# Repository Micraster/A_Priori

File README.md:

# A_Priori
A repository of Modules for A Priori synth. A 5V USB powered modular synth using a Eurorack form factor.

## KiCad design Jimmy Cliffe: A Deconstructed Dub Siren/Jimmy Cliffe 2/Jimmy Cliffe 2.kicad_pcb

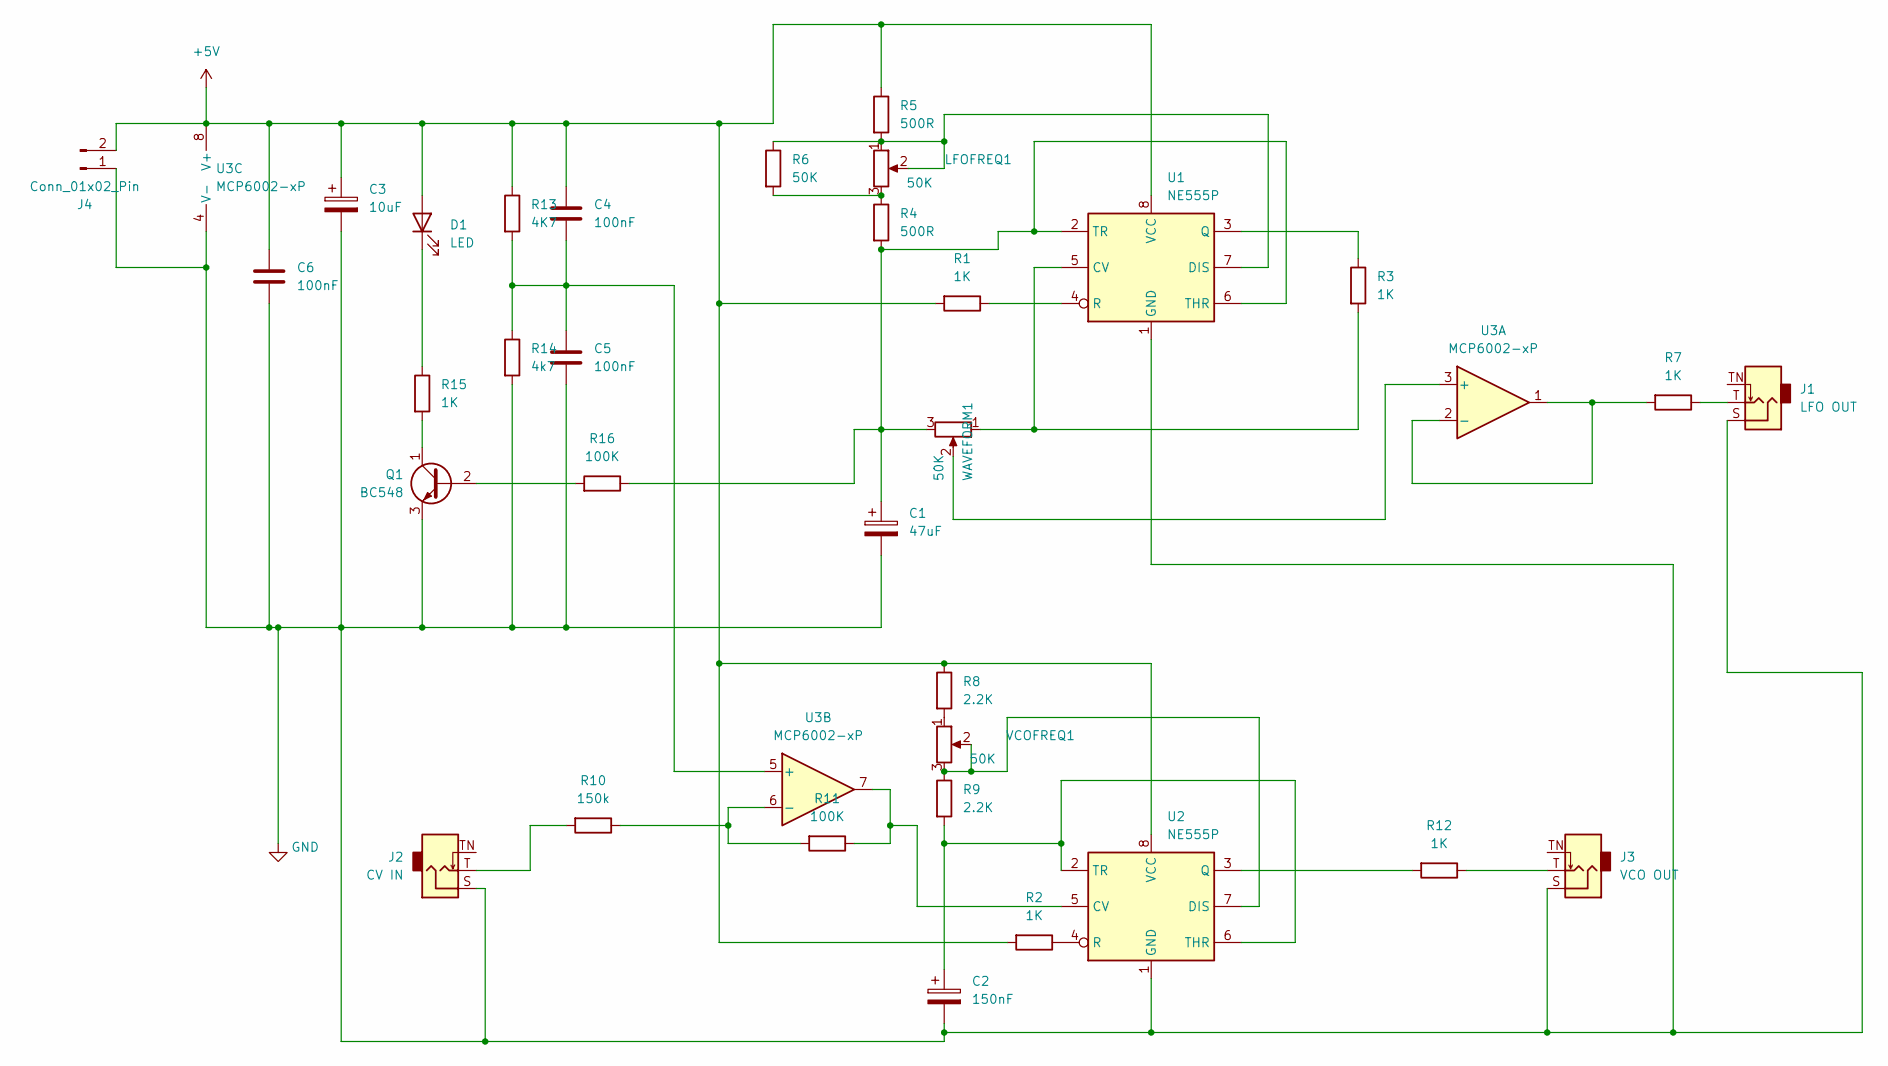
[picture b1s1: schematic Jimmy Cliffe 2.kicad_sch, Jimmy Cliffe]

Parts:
C1: 47uF; CP_Radial_D5.0mm_P2.50mm
C2: 150nF; C_Disc_D6.0mm_W2.5mm_P5.00mm
C3: 10uF; CP_Radial_D5.0mm_P2.50mm
C4, C5, C6: 100nF; C_Disc_D3.8mm_W2.6mm_P2.50mm
D1: LED; LED_D5.0mm
J1: LFO OUT; Jack_3.5mm_QingPu_WQP-PJ398SM_Vertical_CircularHoles
J2: CV IN; Jack_3.5mm_QingPu_WQP-PJ398SM_Vertical_CircularHoles
J3: VCO OUT; Jack_3.5mm_QingPu_WQP-PJ398SM_Vertical_CircularHoles
J4: Conn_01x02_Pin; JST_XH_B2B-XH-A_1x02_P2.50mm_Vertical
LFOFREQ1: 50K; TRIM_RV09AF-40-20K-A10K
Q1: BC548; TO-92_Inline
R1, R2, R3, R7, R12, R15: 1K; R_Axial_DIN0204_L3.6mm_D1.6mm_P7.62mm_Horizontal
R4, R5: 500R; R_Axial_DIN0204_L3.6mm_D1.6mm_P7.62mm_Horizontal
R6: 50K; R_Axial_DIN0204_L3.6mm_D1.6mm_P7.62mm_Horizontal
R8, R9: 2.2K; R_Axial_DIN0204_L3.6mm_D1.6mm_P7.62mm_Horizontal
R10: 150k; R_Axial_DIN0204_L3.6mm_D1.6mm_P7.62mm_Horizontal
R11: 100K; R_Axial_DIN0204_L3.6mm_D1.6mm_P7.62mm_Horizontal
R13: 4K7; R_Axial_DIN0204_L3.6mm_D1.6mm_P7.62mm_Horizontal
R14: 4k7; R_Axial_DIN0204_L3.6mm_D1.6mm_P7.62mm_Horizontal
R16: 100K; R_Axial_DIN0207_L6.3mm_D2.5mm_P7.62mm_Horizontal
U1, U2: NE555P; DIP-8_W7.62mm
U3: MCP6002-xP; DIP-8_W7.62mm
VCOFREQ1: 50K; TRIM_RV09AF-40-20K-A10K
WAVEFORM1: 50K; TRIM_RV09AF-40-20K-A10K

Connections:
+5V: C3.1, C4.1, C6.1, D1.2 (A), J4.2, R1.2, R2.2, R5.1, R8.1, R13.1, U1.8 (VCC), U2.8 (VCC), U3.8 (V+)
GND: C1.2, C2.2, C3.2, C5.2, C6.2, J1.S, J2.S, J3.S, J4.1, Q1.3 (E), R14.2, U1.1 (GND), U2.1 (GND), U3.4 (V-)
unnamed: D1.1 (K), R15.1
unnamed: J1.T, R7.1
unnamed: J2.T, R10.2
unnamed: J3.T, R12.1
unnamed: LFOFREQ1.3, R4.1, R6.2
unnamed: Q1.2 (B), R16.1
unnamed: Q1.1 (C), R15.2
unnamed: R8.2, VCOFREQ1.1
unnamed: R3.2, U1.5 (CV), WAVEFORM1.1
unnamed: LFOFREQ1.1, LFOFREQ1.2, R5.2, R6.1, U1.7 (DIS)
unnamed: R3.1, U1.3 (Q)
unnamed: R1.1, U1.4 (R)
unnamed: C1.1, R4.2, R16.2, U1.2 (TR), U1.6 (THR), WAVEFORM1.3
unnamed: R11.1, U2.5 (CV), U3.7
unnamed: R9.1, U2.7 (DIS), VCOFREQ1.2, VCOFREQ1.3
unnamed: R12.2, U2.3 (Q)
unnamed: R2.1, U2.4 (R)
unnamed: C2.1, R9.2, U2.2 (TR), U2.6 (THR)
unnamed: U3.3 (+), WAVEFORM1.2
unnamed: R7.2, U3.1, U3.2 (-)
unnamed: C4.2, C5.1, R13.2, R14.1, U3.5 (+)
unnamed: R10.1, R11.2, U3.6 (-)

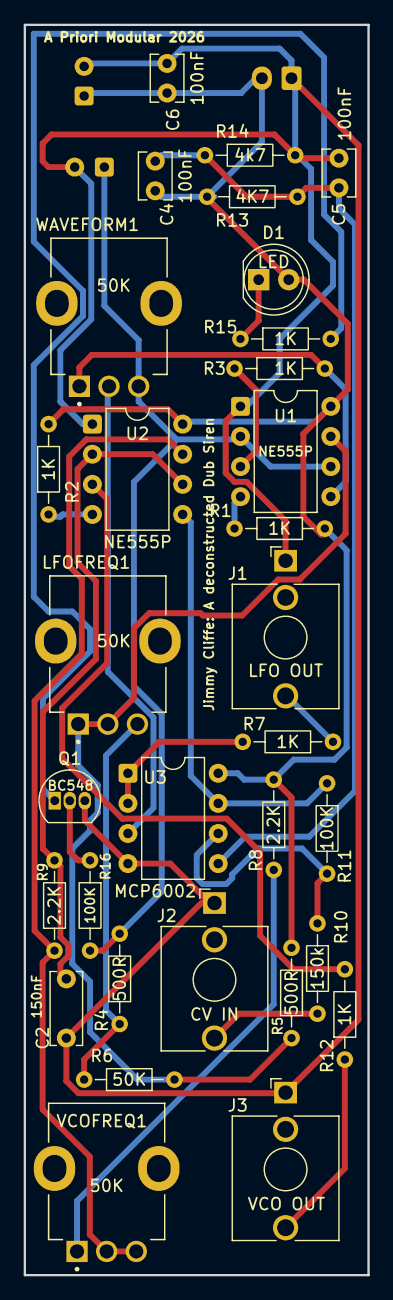
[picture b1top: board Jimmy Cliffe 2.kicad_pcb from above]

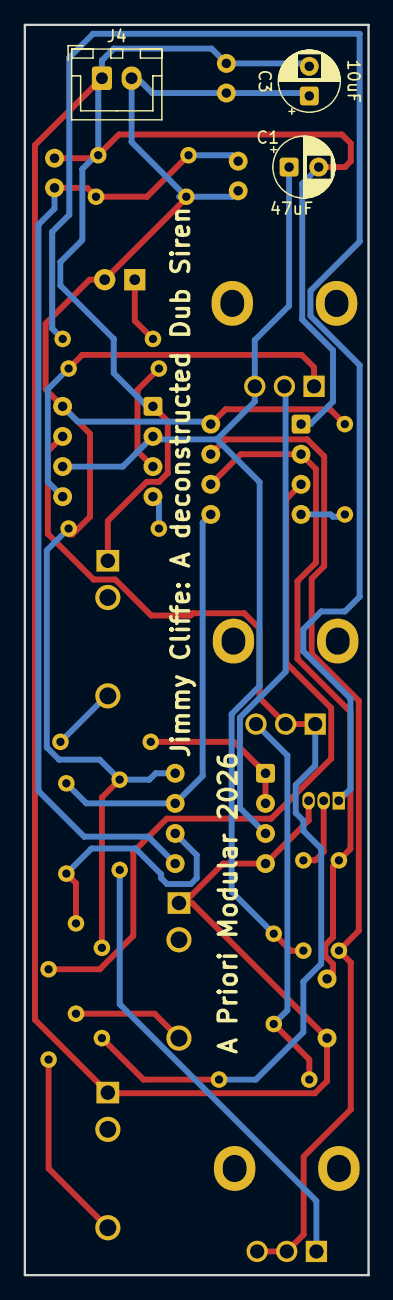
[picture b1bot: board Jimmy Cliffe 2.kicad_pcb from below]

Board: 2 copper layers, 29.0 x 105.5 mm, 34 parts (3 on the bottom side), 24 nets.

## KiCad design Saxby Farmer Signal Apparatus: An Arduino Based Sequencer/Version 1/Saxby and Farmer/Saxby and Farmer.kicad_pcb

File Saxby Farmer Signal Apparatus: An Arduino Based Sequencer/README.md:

John Saxby began his working life as a carpenter at Brighton Station. It was in this role that he developed the first semaphore signals and a system of interlocking for points. The London to Brighton mainline was the effectively the test bed for this system that later spread around the world after the Saxby & Farmer signalling company was established in Hassocks. Saxby designed the iconic raised signal box with a glazed control room, many of which are found on the railway network, including the signal box at Lewes Station.

This module is based on Hagiwo Euclidian (https://www.youtube.com/watch?v=lkoBfiq6KPY) and 6 Channel Gate Sequencer (https://www.youtube.com/watch?v=YszdC8YdFl0).

Like the original this version uses an Arduino Nano but the code is modified to make use of an SPI OLED which allows for a faster refresh rate allowing the module to also function as a basic oscilloscope.

The hardware incorporates an additional input channel to allow an external gate to trigger transistions between sequences and an additional tactile switch to allow the user to select between modes.

The module has 4 Modes 
1) A BPM indicator based on clock pulses as 16th Notes
2) A 6 Channel Sequencer based on the Hagiwo original but with heavily modified code to incorporate a chaining mode, genre presets and a probability function
3) A Euclidian Sequencer
4) Oscilloscope with variable timebase

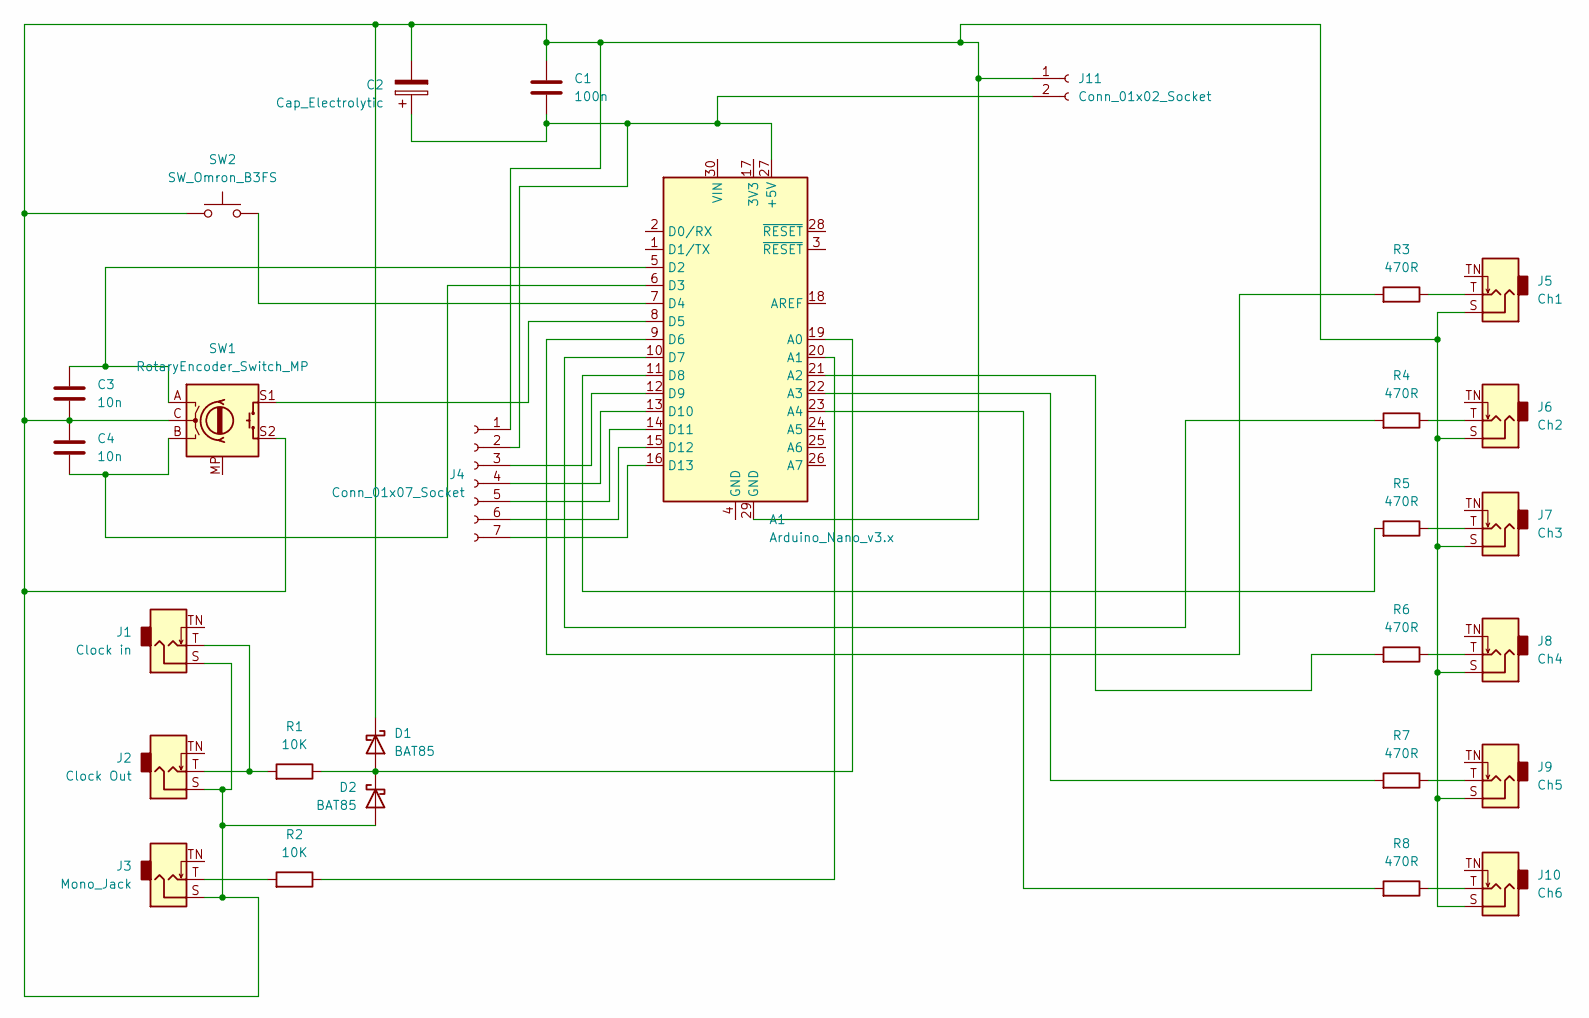
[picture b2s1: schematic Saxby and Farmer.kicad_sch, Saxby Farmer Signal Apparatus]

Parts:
A1: Arduino_Nano_v3.x; Arduino_Nano
C1: 100n; C_Disc_D6.0mm_W2.5mm_P5.00mm
C2: Cap_Electrolytic; CP_Radial_D6.3mm_P2.50mm
C3, C4: 10n; C_Disc_D6.0mm_W2.5mm_P5.00mm
D1, D2: BAT85; D_DO-35_SOD27_P7.62mm_Horizontal
J1: Clock in; Jack_3.5mm_QingPu_WQP-PJ398SM_Vertical_CircularHoles
J2: Clock Out; Jack_3.5mm_QingPu_WQP-PJ398SM_Vertical_CircularHoles
J3: Mono_Jack; Jack_3.5mm_QingPu_WQP-PJ398SM_Vertical_CircularHoles
J4: Conn_01x07_Socket; PinHeader_1x07_P2.54mm_Vertical
J5: Ch1; Jack_3.5mm_QingPu_WQP-PJ398SM_Vertical_CircularHoles
J6: Ch2; Jack_3.5mm_QingPu_WQP-PJ398SM_Vertical_CircularHoles
J7: Ch3; Jack_3.5mm_QingPu_WQP-PJ398SM_Vertical_CircularHoles
J8: Ch4; Jack_3.5mm_QingPu_WQP-PJ398SM_Vertical_CircularHoles
J9: Ch5; Jack_3.5mm_QingPu_WQP-PJ398SM_Vertical_CircularHoles
J10: Ch6; Jack_3.5mm_QingPu_WQP-PJ398SM_Vertical_CircularHoles
J11: Conn_01x02_Socket; JST_XH_B2B-XH-A_1x02_P2.50mm_Vertical
R1, R2: 10K; R_Axial_DIN0207_L6.3mm_D2.5mm_P7.62mm_Horizontal
R3, R4, R5, R6, R7, R8: 470R; R_Axial_DIN0207_L6.3mm_D2.5mm_P7.62mm_Horizontal
SW1: RotaryEncoder_Switch_MP; RotaryEncoder_Alps_EC11E-Switch_Vertical_H20mm_CircularMoun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
SW2: SW_Omron_B3FS; SW_TH_Tactile_Omron_B3F-107x

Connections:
unnamed: A1.27 (+5V), C1.2, C2.1, J4.2, J11.2
unnamed: A1.19 (A0), D1.2 (A), D2.1 (K), R1.2
unnamed: A1.20 (A1), R2.2
unnamed: A1.21 (A2), R6.1
unnamed: A1.22 (A3), R7.1
unnamed: A1.23 (A4), R8.1
unnamed 6: A1.5 (D2), C3.1, SW1.A; also elsewhere on the board
unnamed 7: A1.6 (D3), C4.2, SW1.B; also elsewhere on the board
unnamed: A1.7 (D4), SW2.2
unnamed 9: A1.8 (D5), SW1.S1; also elsewhere on the board
unnamed: A1.9 (D6), R3.1
unnamed: A1.10 (D7), R4.1
unnamed: A1.11 (D8), R5.1
unnamed: A1.12 (D9), J4.3
unnamed: A1.13 (D10), J4.4
unnamed: A1.14 (D11), J4.5
unnamed: A1.15 (D12), J4.6
unnamed: A1.16 (D13), J4.7
unnamed 18: A1.29 (GND), C1.1, C2.2, C3.2, C4.1, D1.1 (K), D2.2 (A), J1.S, J2.S, J3.S, J4.1, J5.S, J6.S, J7.S, J8.S, J9.S, J10.S, J11.1, SW1.C, SW1.S2, SW2.1; also elsewhere on the board
unnamed: J1.T, J2.T, R1.1
unnamed: J3.T, R2.1
unnamed: J5.T, R3.2
unnamed: J6.T, R4.2
unnamed: J7.T, R5.2
unnamed: J8.T, R6.2
unnamed: J9.T, R7.2
unnamed: J10.T, R8.2

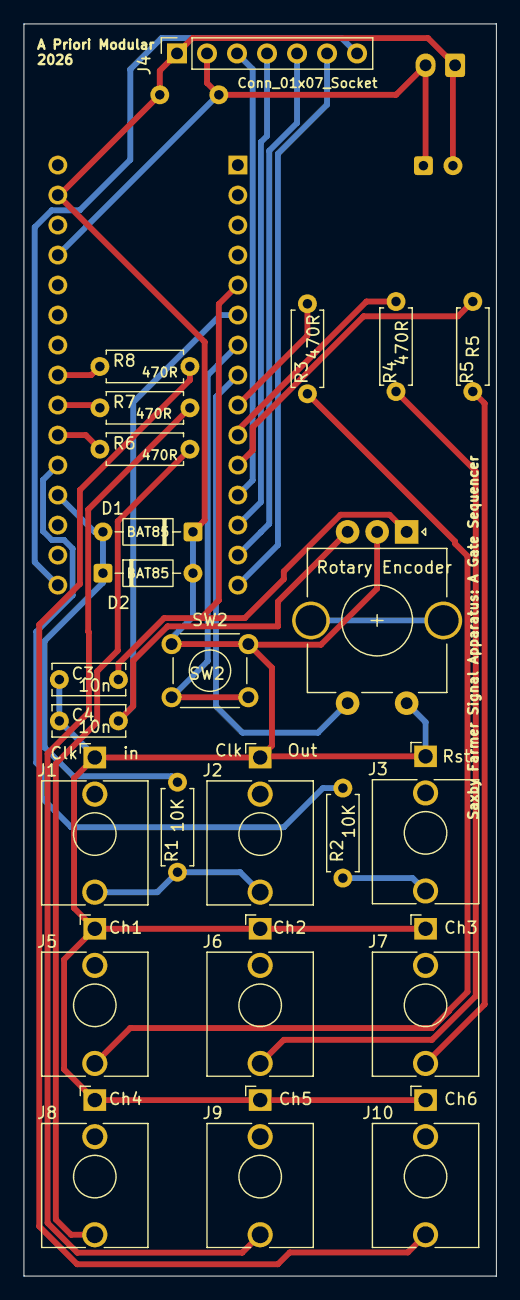
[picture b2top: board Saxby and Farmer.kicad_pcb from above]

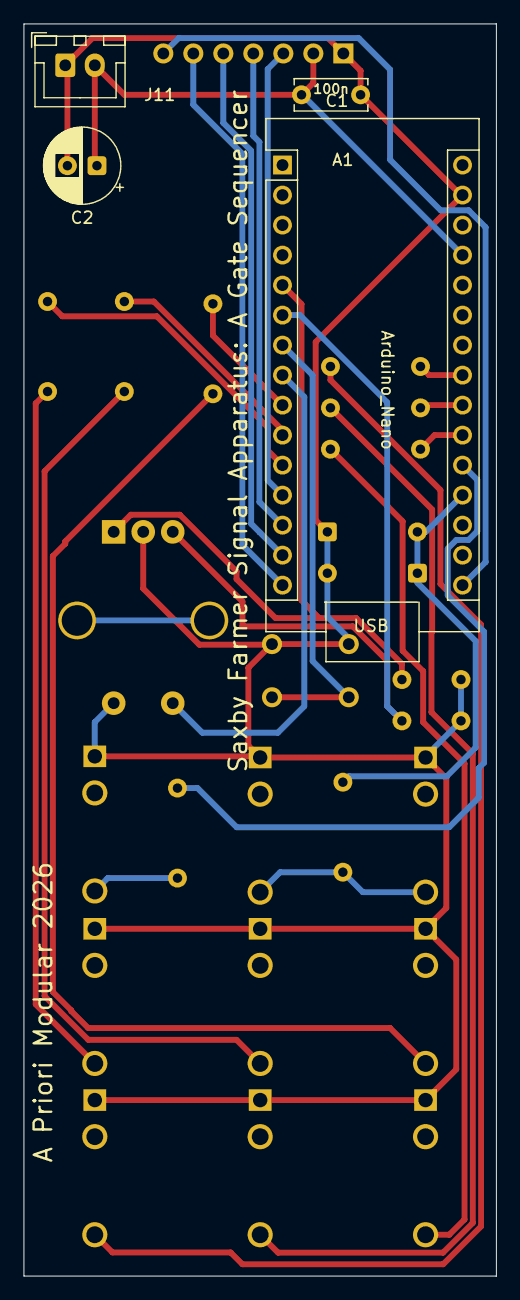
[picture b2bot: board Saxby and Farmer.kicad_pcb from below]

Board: 2 copper layers, 40.0 x 106.0 mm, 28 parts (4 on the bottom side), 27 nets.

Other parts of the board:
Rotary Encoder: RotaryEncoder_Switch_MP; RotaryEncoder_Alps_EC11E-Switch_Vertical_H20mm_CircularMoun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

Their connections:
unnamed 6: Rotary Encoder.A; also elsewhere on the board
unnamed 7: Rotary Encoder.B; also elsewhere on the board
unnamed 9: Rotary Encoder.S1; also elsewhere on the board
unnamed 18: Rotary Encoder.C, Rotary Encoder.S2; also elsewhere on the board

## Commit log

2026-03-28 Create A File and Folder
2026-03-28 img2cpp Signal Box bitmap (white on black)
    Added bitmap data for Lewes Signal Box to PROGMEM.
2026-03-28 Add files via upload
    Monochrome bitmap for splash screen
2026-03-28 Rename Lewes Signal Box .bmp to Lewes Signal Box .bmp
2026-03-28 Rename Lewes Signal Box .bmp to Lewes Signal Box.bmp
2026-03-28 Rename Lewes Signal Box Bitmap Code to Lewes Signal Box Bitmap Code
2026-03-29 VSCode workspace
2026-03-29 Delete Saxby Farmer directory
    Tidying up
2026-03-29 VS Code Workspace
    This is a bit messy
2026-03-29 Delete Saxby Farmer Signal Apparatus: An Arduino Based Sequencer/Prioritron directory
    Uploaded in error
2026-03-29 VS Code Workspace
2026-03-29 Add README with project details and functionality
    Added detailed project description and functionality overview for the Arduino-based sequencer module.
2026-03-29 Update README with version 1.0 error notes
    Added notes about errors and improvements for future versions.
2026-03-29 Fix schematic error in Warning section
    Correct schematic error regarding D1 connection and note on D1 and D2 usage.
2026-03-29 Kicad Files
2026-03-29 Rename README.md to README (Saxby Farmer).md
2026-03-29 Add module details and tribute to Jimmy Cliff
    Added detailed information about the module, its tribute to Jimmy Cliff, and technical specifications for components.
2026-03-29 Update and rename Read Me (Jimmy Cliffe) to Jimmy Cliffe: A Deconstructed Dub Siren/Read Me (Jimmy Cliffe)
2026-03-29 Fix formatting for note on cheap 555 timers
    Corrected formatting for emphasis on the note about cheap 555 timers.
2026-03-29 Fix formatting for note on cheap 555 timers
2026-03-29 Fix formatting of note on cheap 555 timers
2026-03-29 Revise tribute wording in Read Me file
    Updated the tribute wording for the Dub Siren module to clarify its connection to Jimmy Cliff and local heritage.
2026-03-29 Revise readme with heading and text corrections
    Updated the readme to include a heading and corrected minor text errors.
2026-03-29 Fix heading format in README for Dub Siren module
    Corrected heading formatting in the README file.
2026-03-29 Update title formatting in Read Me file
    Removed the heading formatting from the title.
2026-03-29 Update version information and improve clarity
    Emphasize version number and correct errors in Gerbers.
2026-03-29 Kicad including Gerbers
2026-03-29 Jimmy Cliffe 2.0 Schematic
2026-03-29 Rename Jimmy Cliffe 2.0 Schematic to Jimmy Cliffe: A Deconstructed Dub Siren/JJimmy Cliffe 2.0 Schematic
